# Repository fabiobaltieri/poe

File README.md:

PoE Flashlight
==============

http://fabiobaltieri.com/2013/12/29/power-over-ethernet-flashlight/

This project is small PoE flashlight using the TI TPS2378.

License
-------

This work is licensed under a Creative Commons Attribution-ShareAlike 3.0
License.

Contents
--------

    README      this file
    hardware/   source directory for the hardware design

Hardware
--------

All hardware files (schematic, layout and libraries) are in CadSoft Eagle
format.

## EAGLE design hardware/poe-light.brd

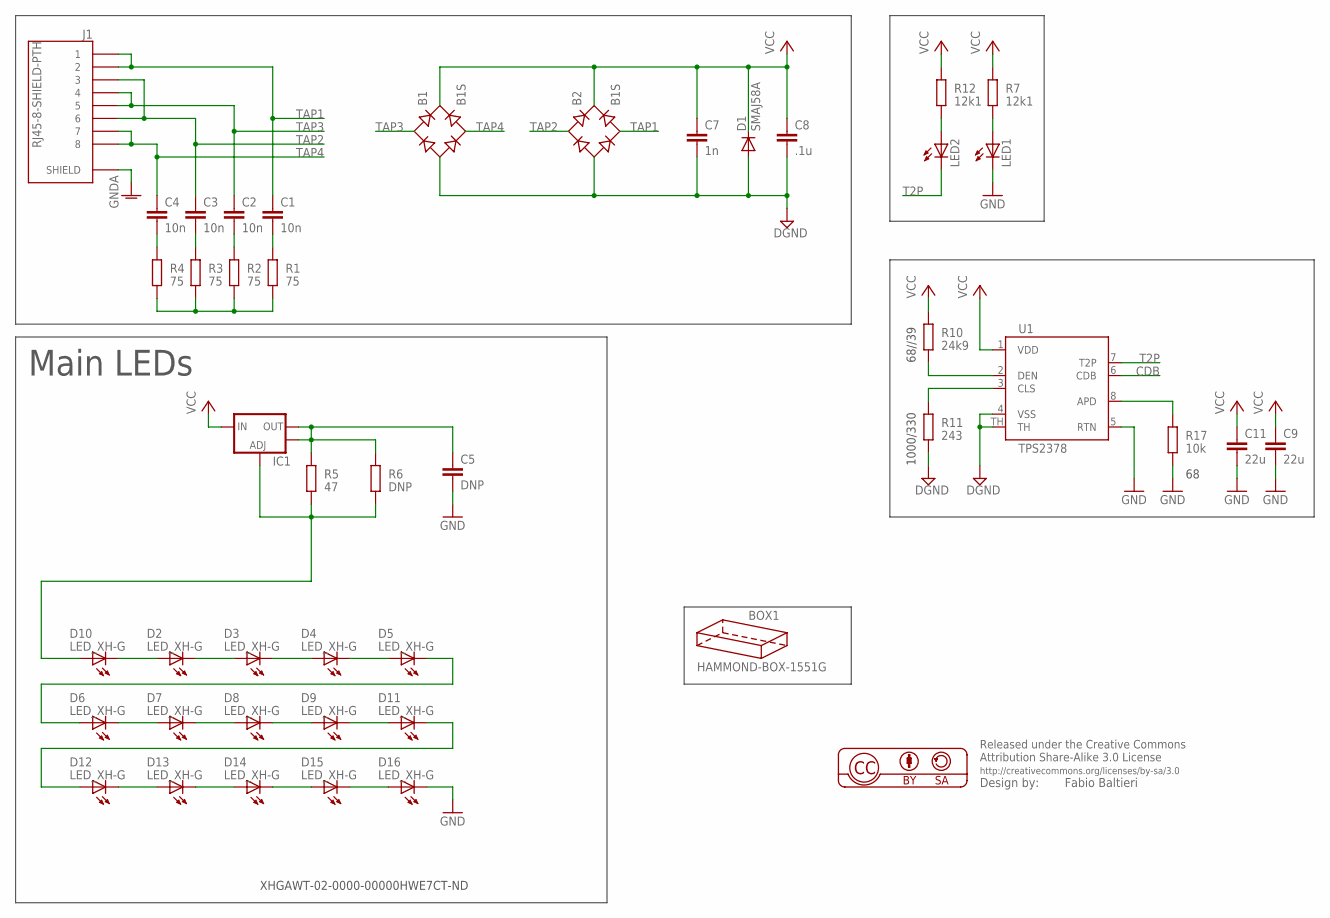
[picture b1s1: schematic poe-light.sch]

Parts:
B1, B2: B1S; MBS
BOX1: HAMMOND-BOX-1551G; 1551G
C1, C2, C3, C4: 10n; C0603
C5: DNP; C0805
C7: 1n; C0603
C8: .1u; C0603
C9, C11: 22u; C1206
D1: SMAJ58A; SMA-DIODE
D2, D3, D4, D5, D6, D7, D8, D9, D10, D11, D12, D13, D14, D15, D16: LED_XH-G; CREE_XHG
IC1: V_REG_LM1117SOT223; SOT223
J1: RJ45-8-SHIELD-PTH; RJ45-8-SHIELD
LED1, LED2: LEDSML0805; SML0805
R1, R2, R3, R4: 75; R0603
R5: 47; R1206
R6: DNP; R1206
R7, R12: 12k1; R0603
R10: 24k9; R0603
R11: 243; R0603
R17: 10k; R0603
U1: TPS2378; SOIC8-POWERPAD

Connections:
CDB: U1.6 (CDB)
DGND: B1.-, B2.-, C7.2, C8.2, D1.A, R11.2, U1.4 (VSS), U1.TH
GND: C5.2, C9.2, C11.2, D16.C, D16.C@1 (C), LED1.C, R17.2, U1.5 (RTN)
GNDA: J1.P$1 (SHIELD), J1.P$2 (SHIELD)
unnamed: LED1.A, R7.2
unnamed: LED2.A, R12.2
unnamed: R10.2, U1.2 (DEN)
unnamed: R11.1, U1.3 (CLS)
unnamed: C5.1, IC1.2 (OUT), IC1.4 (OUT), R5.2, R6.2
unnamed: D10.A, D10.A@1 (A), IC1.1 (ADJ), R5.1, R6.1
unnamed: D5.C, D5.C@1 (C), D6.A, D6.A@1 (A)
unnamed: D11.C, D11.C@1 (C), D12.A, D12.A@1 (A)
unnamed: D2.A, D2.A@1 (A), D10.C, D10.C@1 (C)
unnamed: D2.C, D2.C@1 (C), D3.A, D3.A@1 (A)
unnamed: D3.C, D3.C@1 (C), D4.A, D4.A@1 (A)
unnamed: C4.2, R4.1
unnamed: C3.2, R3.1
unnamed: C2.2, R2.1
unnamed: C1.2, R1.1
unnamed: R1.2, R2.2, R3.2, R4.2
unnamed: D4.C, D4.C@1 (C), D5.A, D5.A@1 (A)
unnamed: D6.C, D6.C@1 (C), D7.A, D7.A@1 (A)
unnamed: D7.C, D7.C@1 (C), D8.A, D8.A@1 (A)
unnamed: D8.C, D8.C@1 (C), D9.A, D9.A@1 (A)
unnamed: D9.C, D9.C@1 (C), D11.A, D11.A@1 (A)
unnamed: D12.C, D12.C@1 (C), D13.A, D13.A@1 (A)
unnamed: D13.C, D13.C@1 (C), D14.A, D14.A@1 (A)
unnamed: D14.C, D14.C@1 (C), D15.A, D15.A@1 (A)
unnamed: D15.C, D15.C@1 (C), D16.A, D16.A@1 (A)
unnamed: R17.1, U1.8 (APD)
T2P: LED2.C, U1.7 (T2P)
TAP1: B2.AC2, C1.1, J1.1, J1.2
TAP2: B2.AC1, C3.1, J1.3, J1.6
TAP3: B1.AC1, C2.1, J1.4, J1.5
TAP4: B1.AC2, C4.1, J1.7, J1.8
VCC: B1.+, B2.+, C7.1, C8.1, C9.1, C11.1, D1.C, IC1.3 (IN), R7.1, R10.1, R12.1, U1.1 (VDD)

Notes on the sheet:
XHGAWT-02-0000-00000HWE7CT-ND
Main LEDs
68//39
1000/330

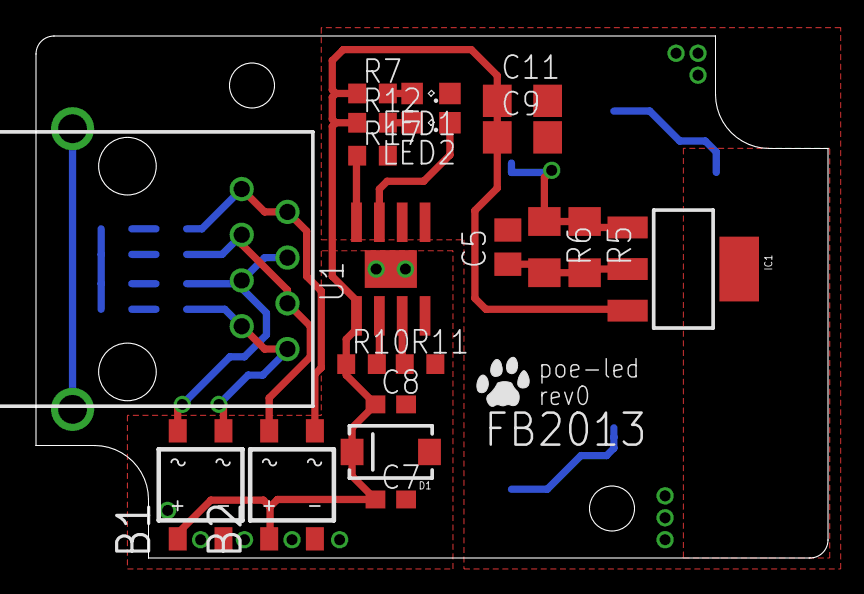
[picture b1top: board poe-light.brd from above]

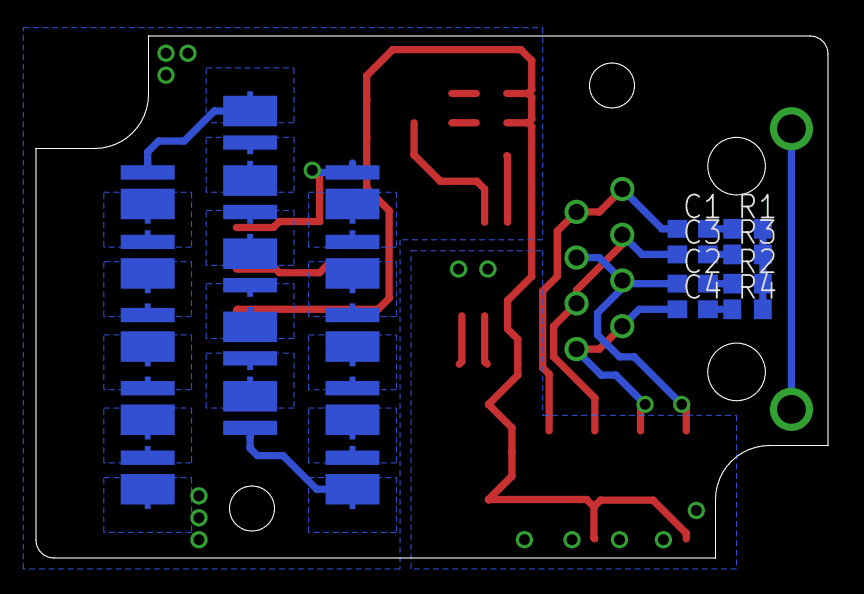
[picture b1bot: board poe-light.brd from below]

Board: 2 copper layers, 44.0 x 29.0 mm, 45 parts (23 on the bottom side), 35 nets.

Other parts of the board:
U$1: CAT-L

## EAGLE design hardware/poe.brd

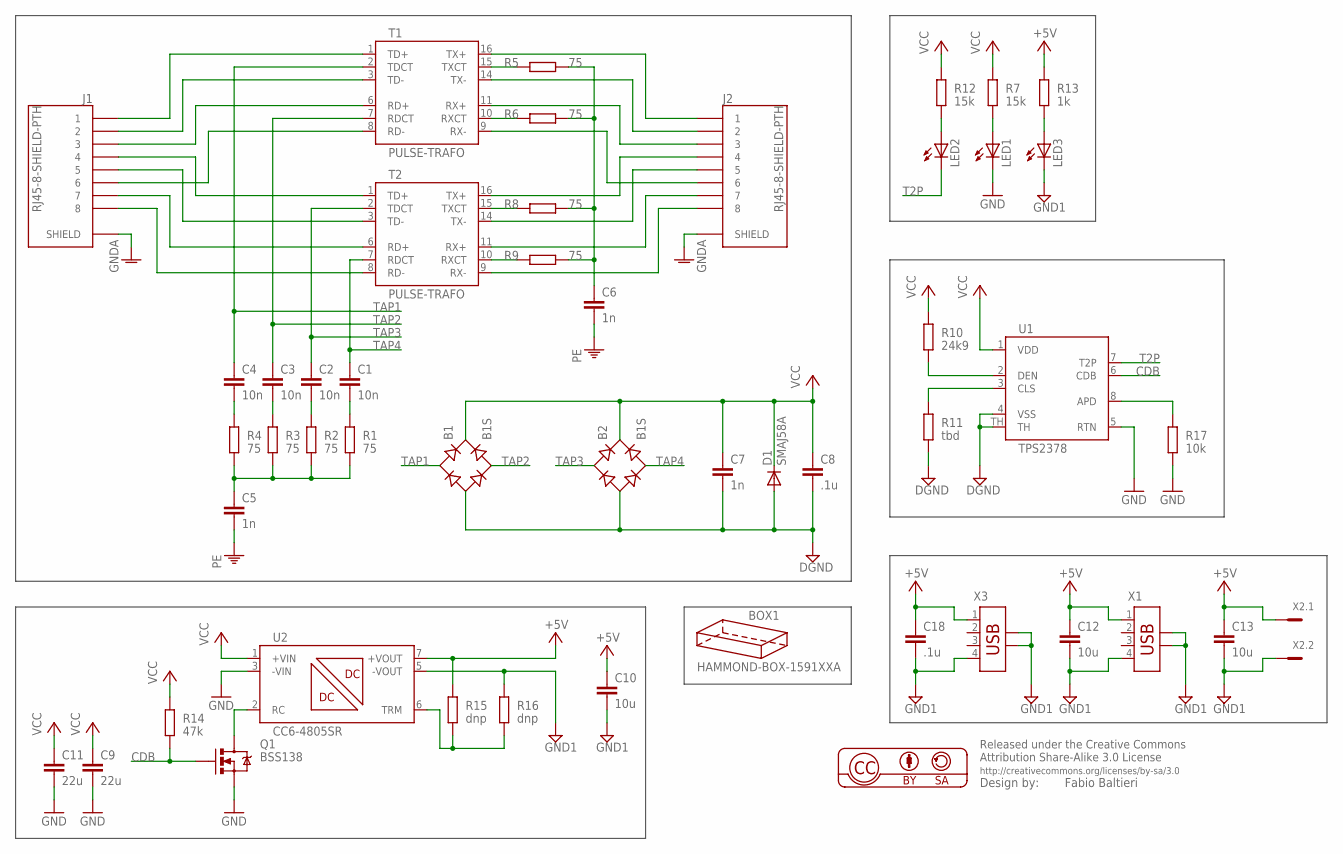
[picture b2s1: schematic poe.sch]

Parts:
B1, B2: B1S; MBS
BOX1: HAMMOND-BOX-1591XXA; 1591XXA
C1, C2, C3, C4: 10n; C0603
C5, C6, C7: 1n; C0603
C8, C18: .1u; C0603
C9, C11: 22u; C1206
C10: 10u; C0805
C12, C13: 10u; C0603
D1: SMAJ58A; SMA-DIODE
J1, J2: RJ45-8-SHIELD-PTH; RJ45-8-SHIELD
LED1, LED2, LED3: LEDSML0805; SML0805
Q1: BSS138; SOT23-3
R1, R2, R3, R4, R5, R6, R8, R9: 75; R0603
R7, R12: 15k; R0603
R10: 24k9; R0603
R11: tbd; R0603
R13: 1k; R0603
R14: 47k; R0603
R15, R16: dnp; R0603
R17: 10k; R0603
T1, T2: PULSE-TRAFO
U1: TPS2378; SOIC8-POWERPAD
U2: CC6-4805SR; CC6-XXXXSR-E
X1, X3: USB-787616; USB
X2: MC2

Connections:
+5V: C10.1, C12.1, C13.1, C18.1, R13.1, R15.1, U2.7 (+VOUT), X1.1, X2.1, X3.1
CDB: Q1.1 (G), R14.2, U1.6 (CDB)
DGND: B1.-, B2.-, C7.2, C8.2, D1.A, R11.2, U1.4 (VSS), U1.TH
GND: C9.2, C11.2, LED1.C, Q1.2 (S), R17.2, U1.5 (RTN), U2.3 (-VIN)
GND1: C10.2, C12.2, C13.2, C18.2, LED3.C, R16.1, U2.5 (-VOUT), X1.4, X1.SHLD1, X1.SHLD2, X2.2, X3.4, X3.SHLD1, X3.SHLD2
GNDA: J1.P$1 (SHIELD), J1.P$2 (SHIELD), J2.P$1 (SHIELD), J2.P$2 (SHIELD)
unnamed: LED1.A, R7.2
unnamed: LED2.A, R12.2
unnamed: R10.2, U1.2 (DEN)
unnamed: R11.1, U1.3 (CLS)
unnamed: J1.1, T1.1 (TD+)
unnamed: J1.2, T1.3 (TD-)
unnamed: J1.3, T1.6 (RD+)
unnamed: J1.6, T1.8 (RD-)
unnamed: J1.4, T2.1 (TD+)
unnamed: J1.5, T2.3 (TD-)
unnamed: J1.7, T2.6 (RD+)
unnamed: J1.8, T2.8 (RD-)
unnamed: C4.2, R4.1
unnamed: C3.2, R3.1
unnamed: C2.2, R2.1
unnamed: C1.2, R1.1
unnamed: C5.1, R1.2, R2.2, R3.2, R4.2
unnamed: R5.1, T1.15 (TXCT)
unnamed: R6.1, T1.10 (RXCT)
unnamed: R8.1, T2.15 (TXCT)
unnamed: R9.1, T2.10 (RXCT)
unnamed: C6.1, R5.2, R6.2, R8.2, R9.2
unnamed: J2.1, T1.16 (TX+)
unnamed: J2.2, T1.14 (TX-)
unnamed: J2.3, T1.11 (RX+)
unnamed: J2.6, T1.9 (RX-)
unnamed: J2.4, T2.16 (TX+)
unnamed: J2.5, T2.14 (TX-)
unnamed: J2.7, T2.11 (RX+)
unnamed: J2.8, T2.9 (RX-)
unnamed: LED3.A, R13.2
unnamed: Q1.3 (D), U2.2 (RC)
unnamed: R15.2, R16.2, U2.6 (TRM)
unnamed: R17.1, U1.8 (APD)
PE: C5.2, C6.2
T2P: LED2.C, U1.7 (T2P)
TAP1: B1.AC1, C4.1, T1.2 (TDCT)
TAP2: B1.AC2, C3.1, T1.7 (RDCT)
TAP3: B2.AC1, C2.1, T2.2 (TDCT)
TAP4: B2.AC2, C1.1, T2.7 (RDCT)
VCC: B1.+, B2.+, C7.1, C8.1, C9.1, C11.1, D1.C, R7.1, R10.1, R12.1, R14.1, U1.1 (VDD), U2.1 (+VIN)

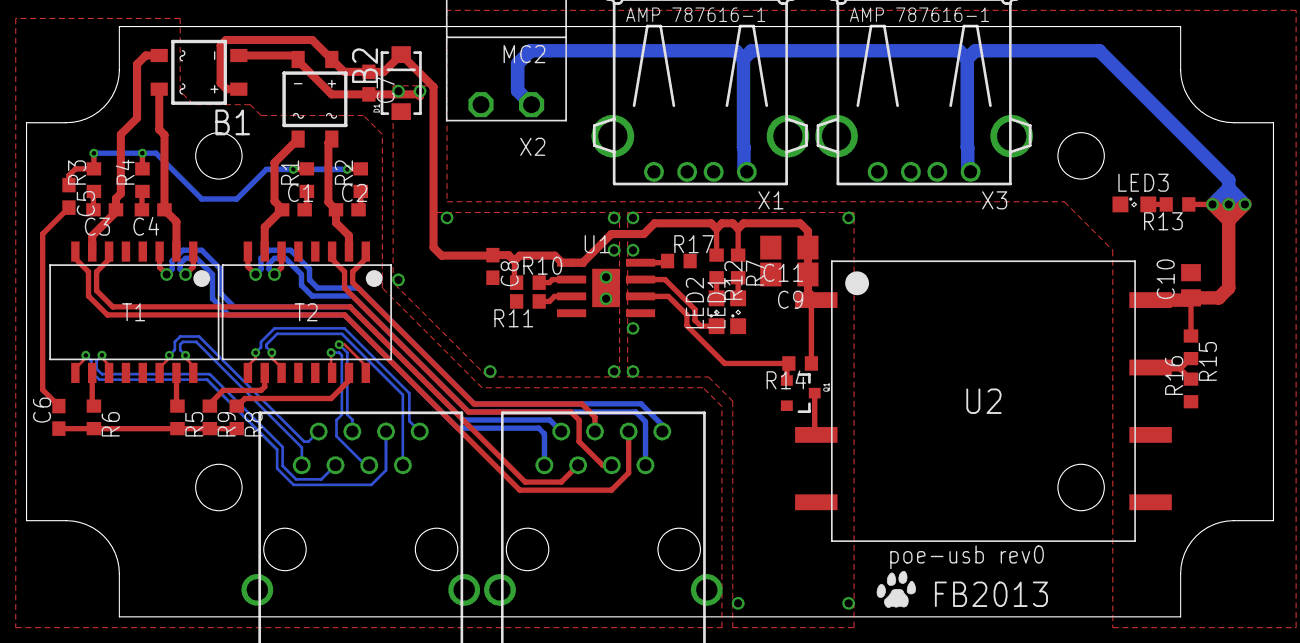
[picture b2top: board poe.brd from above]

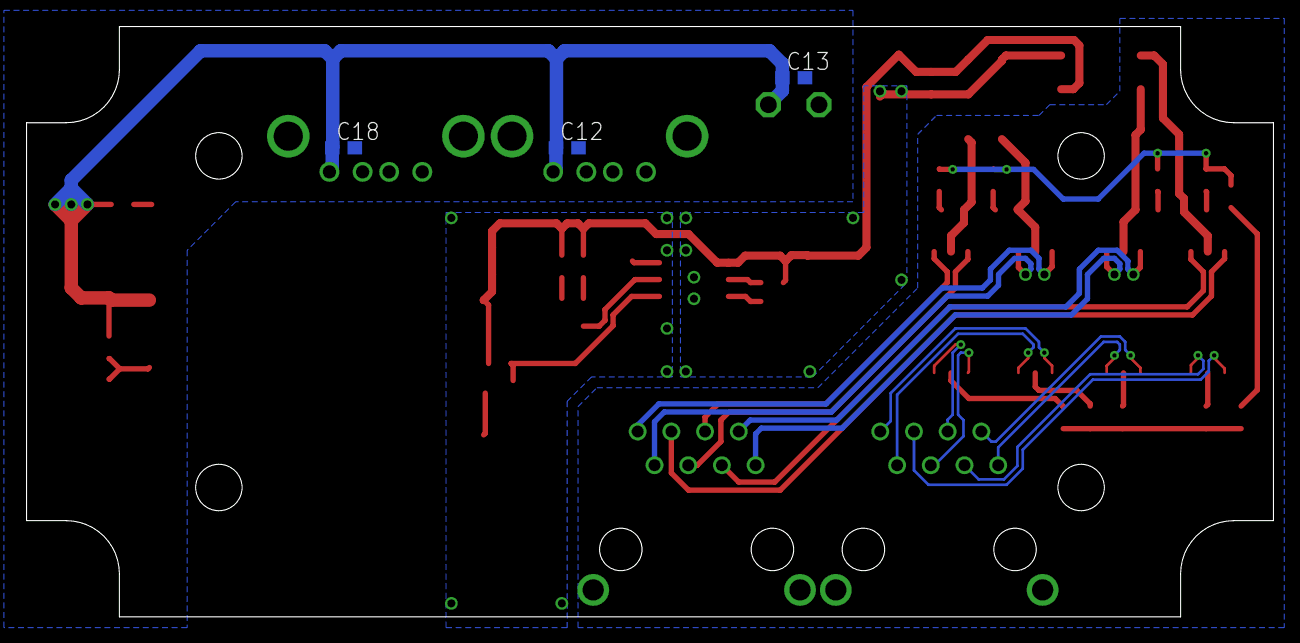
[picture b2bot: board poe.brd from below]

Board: 2 copper layers, 94.0 x 44.5 mm, 49 parts (3 on the bottom side), 47 nets.

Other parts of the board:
U$2: CAT-L

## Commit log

2013-11-06 poe: update some values
2013-12-05 hw: adjusted resistor values, added notes about //
2013-12-07 hw: sch: layout clean
2013-12-07 hw: add poe-light.pdf
2013-12-07 add README
2013-12-29 README: add blog post link

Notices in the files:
parts and their libraries:
SparkFun-DiscreteSemi: Licensing: CC v3.0 Share-Alike You are welcome to use this library for commercial purposes.
balto: Released under the Creative Commons
balto: http://creativecommons.org/licenses/by-sa/3.0
